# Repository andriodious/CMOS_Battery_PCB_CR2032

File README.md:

# CMOS_Battery_PCB_CR2032

Allows a safer CR2032 battery backed clock/CMOS RAM alternative to Varta PCB mounted solution.

Can be used with existing PCB charging circuitry as it includes a blocking diode. This board will NOT charge the coin cell.

PCB is designed to be mounted separately from main PCB, with flying leads providing power to PCB battery socket.

This board has so far been tested on machines equipped with the Philips PCF8583T chip.

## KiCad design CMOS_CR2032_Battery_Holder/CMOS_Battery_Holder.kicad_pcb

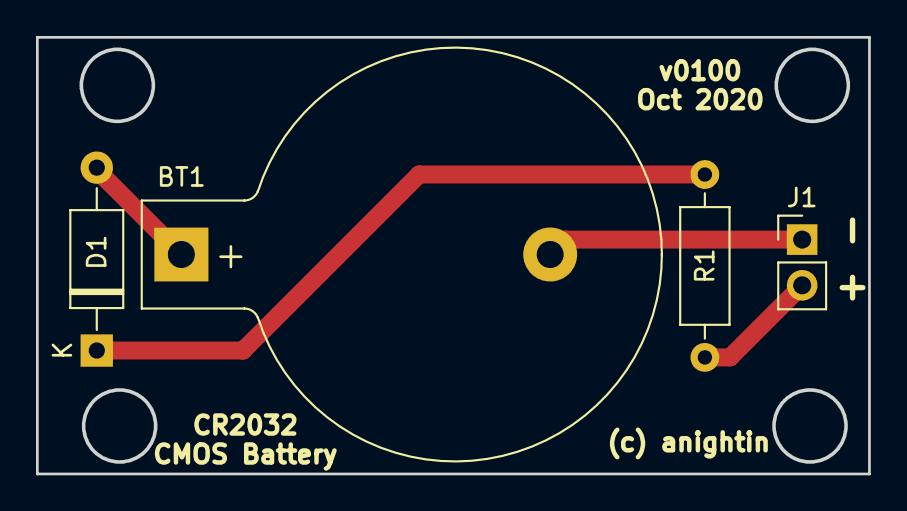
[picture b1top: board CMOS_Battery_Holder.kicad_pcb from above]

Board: 2 copper layers, 46.2 x 24.3 mm, 4 parts (0 on the bottom side), 4 nets.

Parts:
BT1: CR2032_3V; BatteryHolder_Keystone_103_1x20mm
D1: D_Schottky; D_A-405_P10.16mm_Horizontal
J1: Conn_01x02_Female; PinHeader_1x02_P2.54mm_Vertical
R1: 4K7; R_Axial_DIN0207_L6.3mm_D2.5mm_P10.16mm_Horizontal

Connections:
/BATtoD1: BT1.1, D1.2
/D1toR1: D1.1, R1.2
/Neg: BT1.2, J1.1
/Pos: J1.2, R1.1
